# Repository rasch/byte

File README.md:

# byte

![The byte Keyboard, Version 0.1.0][image]

An 8-key, one-handed, business card sized keyboard.

- Keyboard Maintainer: [rasch](https://github.com/rasch/byte)
- Hardware Supported: Byte 0.1.0 (stm32f072)
- Hardware Availability: [byte]

## Getting Board

Check out [the byte releases page][releases] for the required files to get
PCBs manufactured (`plot.zip`) and/or assembled (`bom.csv` and `cpl.csv`). For
those with soldering abilities, an interactive BOM/CPL HTML file (`ibom.html`)
is provided to aid with self-assembly.

During development, it may be preferable (faster) to run rule checks and test
builds locally. There is a `run` shell script in the root of this repository
that is used by the CI/CD for building releases. This script can be run
directly (`./run pcb`), but it requires the `kicad-cli` 8.0+ release to be
installed. Instead, if `podman` is available, it is recommended to use the
`build` script. This script just runs the `./run` script in the
`kicad/kicad:8.0` container. The build files and reports (ERC/DRC) are placed in
the `dist` directory.

![The byte Keyboard, Version 0.1.0][image-back]

In addition to the parts listed in the BOM, the following will be needed for a
complete keyboard:

- 8 x Kailh Low Profile Choc Switches (PG1350)
- 8 x 1u Choc Keycaps (such as MBK)
- USB-C cable to connect to device
- Some rubber feet or neoprene adhesive rubber pads to prevent the board from
  sliding all over the place

## Firmware Installation

Download the firmware, `byte_left.bin` or `byte_right.bin`, from [the byte
releases page][releases]. To flash the keyboard, press the reset button on the
PCB to enter bootloader mode, then run:

```sh
# left-handed artsey
dfu-util -a 0 -d 0483:DF11 -s 0x8000000:leave -D byte_left.bin

# or right-handed artsey
dfu-util -a 0 -d 0483:DF11 -s 0x8000000:leave -D byte_right.bin
```

For details on compiling the firmware, please see the [Github Actions
workflow][build].

## Keymap

The firmware, `byte_left.bin` and `byte_right.bin`, keymaps are based on the
[ARTSEY v0.9.0][artsey] layout. This layout is of limited use for most people,
but it's fun to learn and very useful for those with certain disabilities. The
firmware keymap configuration, `fw/keymaps/left/keymap.c`, provides a good
starting point for making the byte yours! It can be a macropad for your favorite
game, for drawing with Inkscape, for designing keyboards with KiCad, or even
making PowerPoint presentations (Ew!). Check out the [QMK documentation][qmk] to
get inspiration for your own macropad layout!

## License

[Solderpad Hardware License v2.1](LICENSE)

[byte]: https://github.com/rasch/byte
[releases]: https://github.com/rasch/byte/releases/
[image]: https://i.imgur.com/48yj4tK.jpg
[image-back]: https://i.imgur.com/SwSe1no.jpg
[build]: https://github.com/rasch/byte/blob/main/.github/workflows/fw.yml
[artsey]: https://artsey.io/
[qmk]: https://docs.qmk.fm/#/

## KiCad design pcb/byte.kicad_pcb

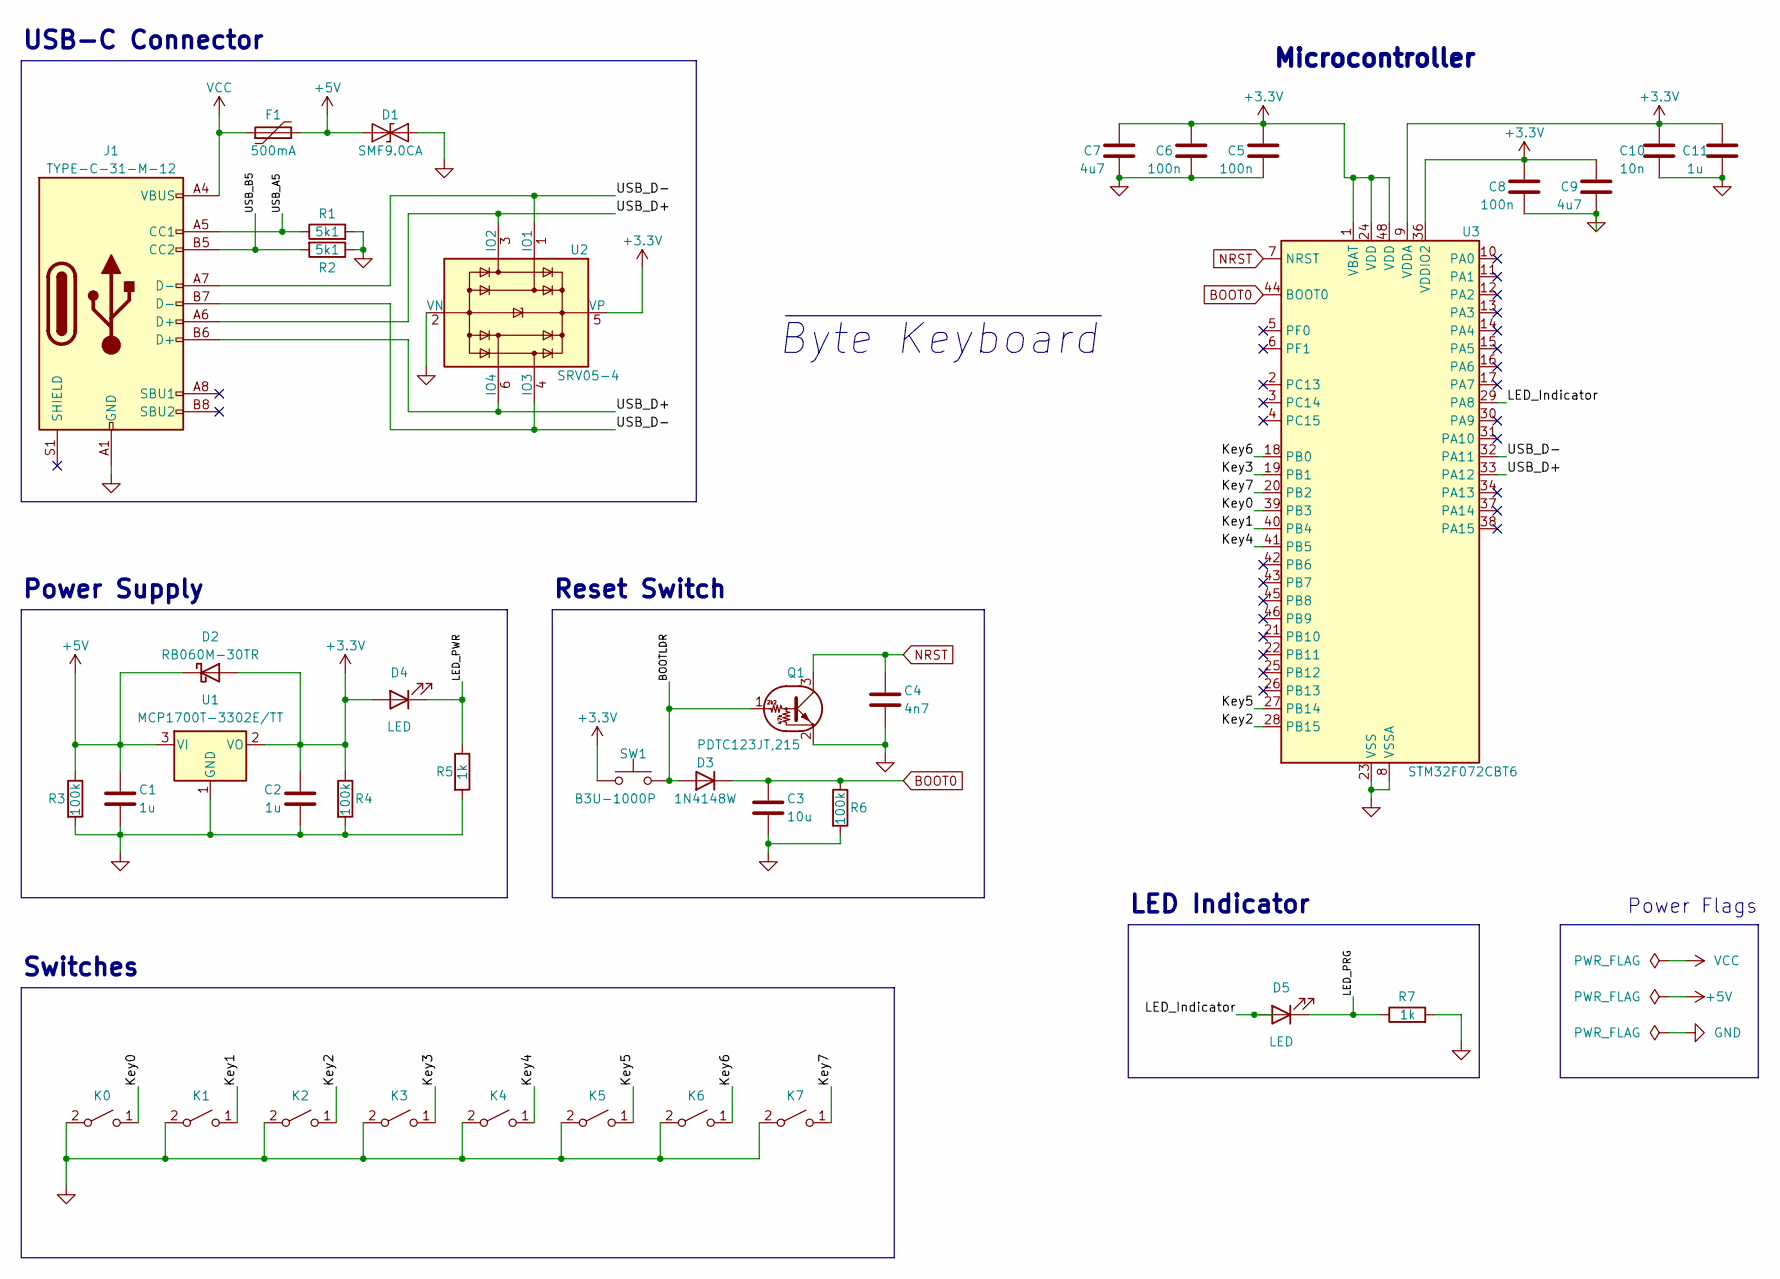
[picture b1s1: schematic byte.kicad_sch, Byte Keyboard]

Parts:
C1, C2, C11: 1u; C_0805_2012Metric; Part Name Capacitor; LCSC Part C28323
C3: 10u; C_0805_2012Metric; Part Name Capacitor; LCSC Part C17024
C4: 4n7; C_0805_2012Metric; Part Name Capacitor; LCSC Part C717014
C5, C6, C8: 100n; C_0805_2012Metric; Part Name Capacitor; LCSC Part C49678
C7, C9: 4u7; C_0805_2012Metric; Part Name Capacitor; LCSC Part C87998
C10: 10n; C_0805_2012Metric; Part Name Capacitor; LCSC Part C1710
D1: SMF9.0CA; D_SOD-123; Part Name Bidirectional Diode; LCSC Part C435473
D2: RB060M-30TR; D_SOD-123; Part Name Schottky Barrier Diodes; LCSC Part C559324
D3: 1N4148W; D_SOD-123; Part Name Diode; LCSC Part C81598
D4, D5: LED; LED_0603_1608Metric; Part Name Red LED; LCSC Part C84263
F1: 500mA; Fuse_1206_3216Metric; Part Name Polyfuse; LCSC Part C151162
J1: TYPE-C-31-M-12; USB_C_Receptacle_HRO_TYPE-C-31-M-12; Part Name USB C; LCSC Part C165948
K0, K1, K2, K3, K4, K5, K6, K7: SW_KEY; Choc_PG1350_Choc_Spacing
Q1: PDTC123JT,215; SOT-23; Part Name NPN Transistor; LCSC Part C406040
R1, R2: 5k1; R_0805_2012Metric; Part Name Resistor; LCSC Part C27834
R3, R4, R6: 100k; R_0805_2012Metric; Part Name Resistor; LCSC Part C149504
R5, R7: 1k; R_0805_2012Metric; Part Name Resistor; LCSC Part C25318
SW1: B3U-1000P; SW_SPST_B3U-1000P; Part Name Reset Button; LCSC Part C231329
U1: MCP1700T-3302E/TT; SOT-23; Part Name Dropout Regulator; LCSC Part C39051
U2: SRV05-4; SOT-23-6; Part Name TVS Diode Array; LCSC Part C558418
U3: STM32F072CBT6; LQFP-48_7x7mm_P0.5mm; Part Name MCU; LCSC Part C81720

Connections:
+3.3V: C2.1, C5.1, C6.2, C7.1, C8.2, C9.2, C10.2, C11.2, D2.2 (A), D4.2 (A), R4.1, SW1.1, U1.2 (VO), U2.5 (VP), U3.1 (VBAT), U3.9 (VDDA), U3.24 (VDD), U3.36 (VDDIO2), U3.48 (VDD)
+5V: C1.1, D1.1 (A1), D2.1 (K), F1.2, R3.1, U1.3 (VI)
/BOOTLDR: D3.2 (A), Q1.1 (B), SW1.2
/Key0: K0.1 (A), U3.39 (PB3)
/Key1: K1.1 (A), U3.40 (PB4)
/Key2: K2.1 (A), U3.28 (PB15)
/Key3: K3.1 (A), U3.19 (PB1)
/Key4: K4.1 (A), U3.41 (PB5)
/Key5: K5.1 (A), U3.27 (PB14)
/Key6: K6.1 (A), U3.18 (PB0)
/Key7: K7.1 (A), U3.20 (PB2)
/LED_Indicator: D5.2 (A), U3.29 (PA8)
/LED_PRG: D5.1 (K), R7.1
/LED_PWR: D4.1 (K), R5.1
/USB_A5: J1.A5 (CC1), R1.1
/USB_B5: J1.B5 (CC2), R2.2
/USB_D+: J1.A6 (D+), J1.B6 (D+), U2.3 (IO2), U2.6 (IO4), U3.33 (PA12)
/USB_D-: J1.A7 (D-), J1.B7 (D-), U2.1 (IO1), U2.4 (IO3), U3.32 (PA11)
BOOT0: C3.2, D3.1 (K), R6.1, U3.44 (BOOT0)
GND: C1.2, C2.2, C3.1, C4.2, C5.2, C6.1, C7.2, C8.1, C9.1, C10.1, C11.1, D1.2 (A2), J1.A1 (GND), J1.A12 (GND), J1.B1 (GND), J1.B12 (GND), K0.2 (B), K1.2 (B), K2.2 (B), K3.2 (B), K4.2 (B), K5.2 (B), K6.2 (B), K7.2 (B), Q1.2 (E), R1.2, R2.1, R3.2, R4.2, R5.2, R6.2, R7.2, U1.1 (GND), U2.2 (VN), U3.8 (VSSA), U3.23 (VSS), U3.35 (VSS), U3.47 (VSS)
NRST: C4.1, Q1.3 (C), U3.7 (NRST)
VCC: F1.1, J1.A4 (VBUS), J1.A9 (VBUS), J1.B4 (VBUS), J1.B9 (VBUS)

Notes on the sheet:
LED Indicator
Power Flags
Switches
~{${TITLE}}
USB-C Connector
Power Supply
Microcontroller
Reset Switch

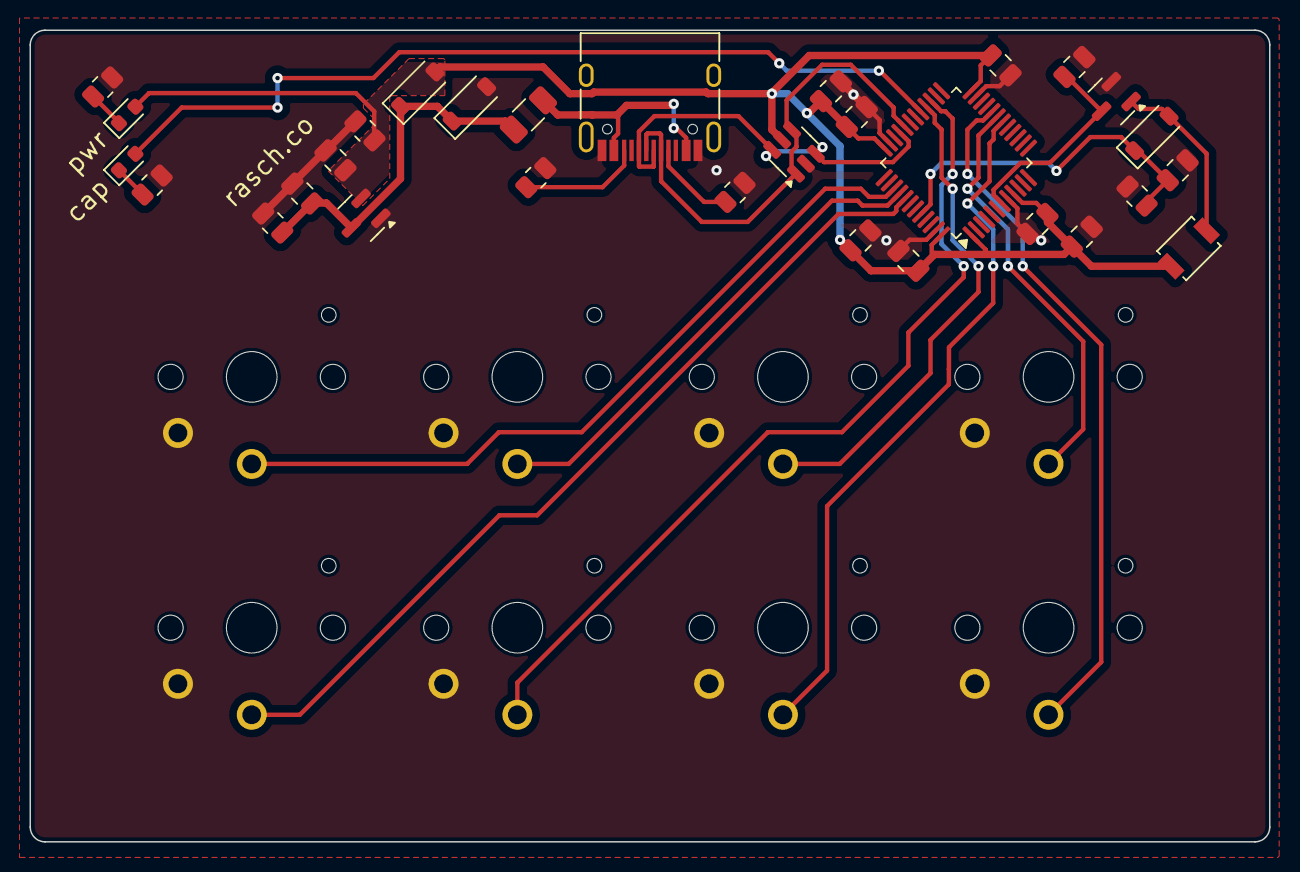
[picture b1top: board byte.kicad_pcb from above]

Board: 2 copper layers, 84.0 x 55.0 mm, 38 parts (0 on the bottom side), 22 nets.

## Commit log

2024-06-17 🎉 Initial commit
2024-06-18 🚀 Initial release
2024-06-18 🐛 Fix typo in CI config
2024-06-18 🎨 Add art assets
